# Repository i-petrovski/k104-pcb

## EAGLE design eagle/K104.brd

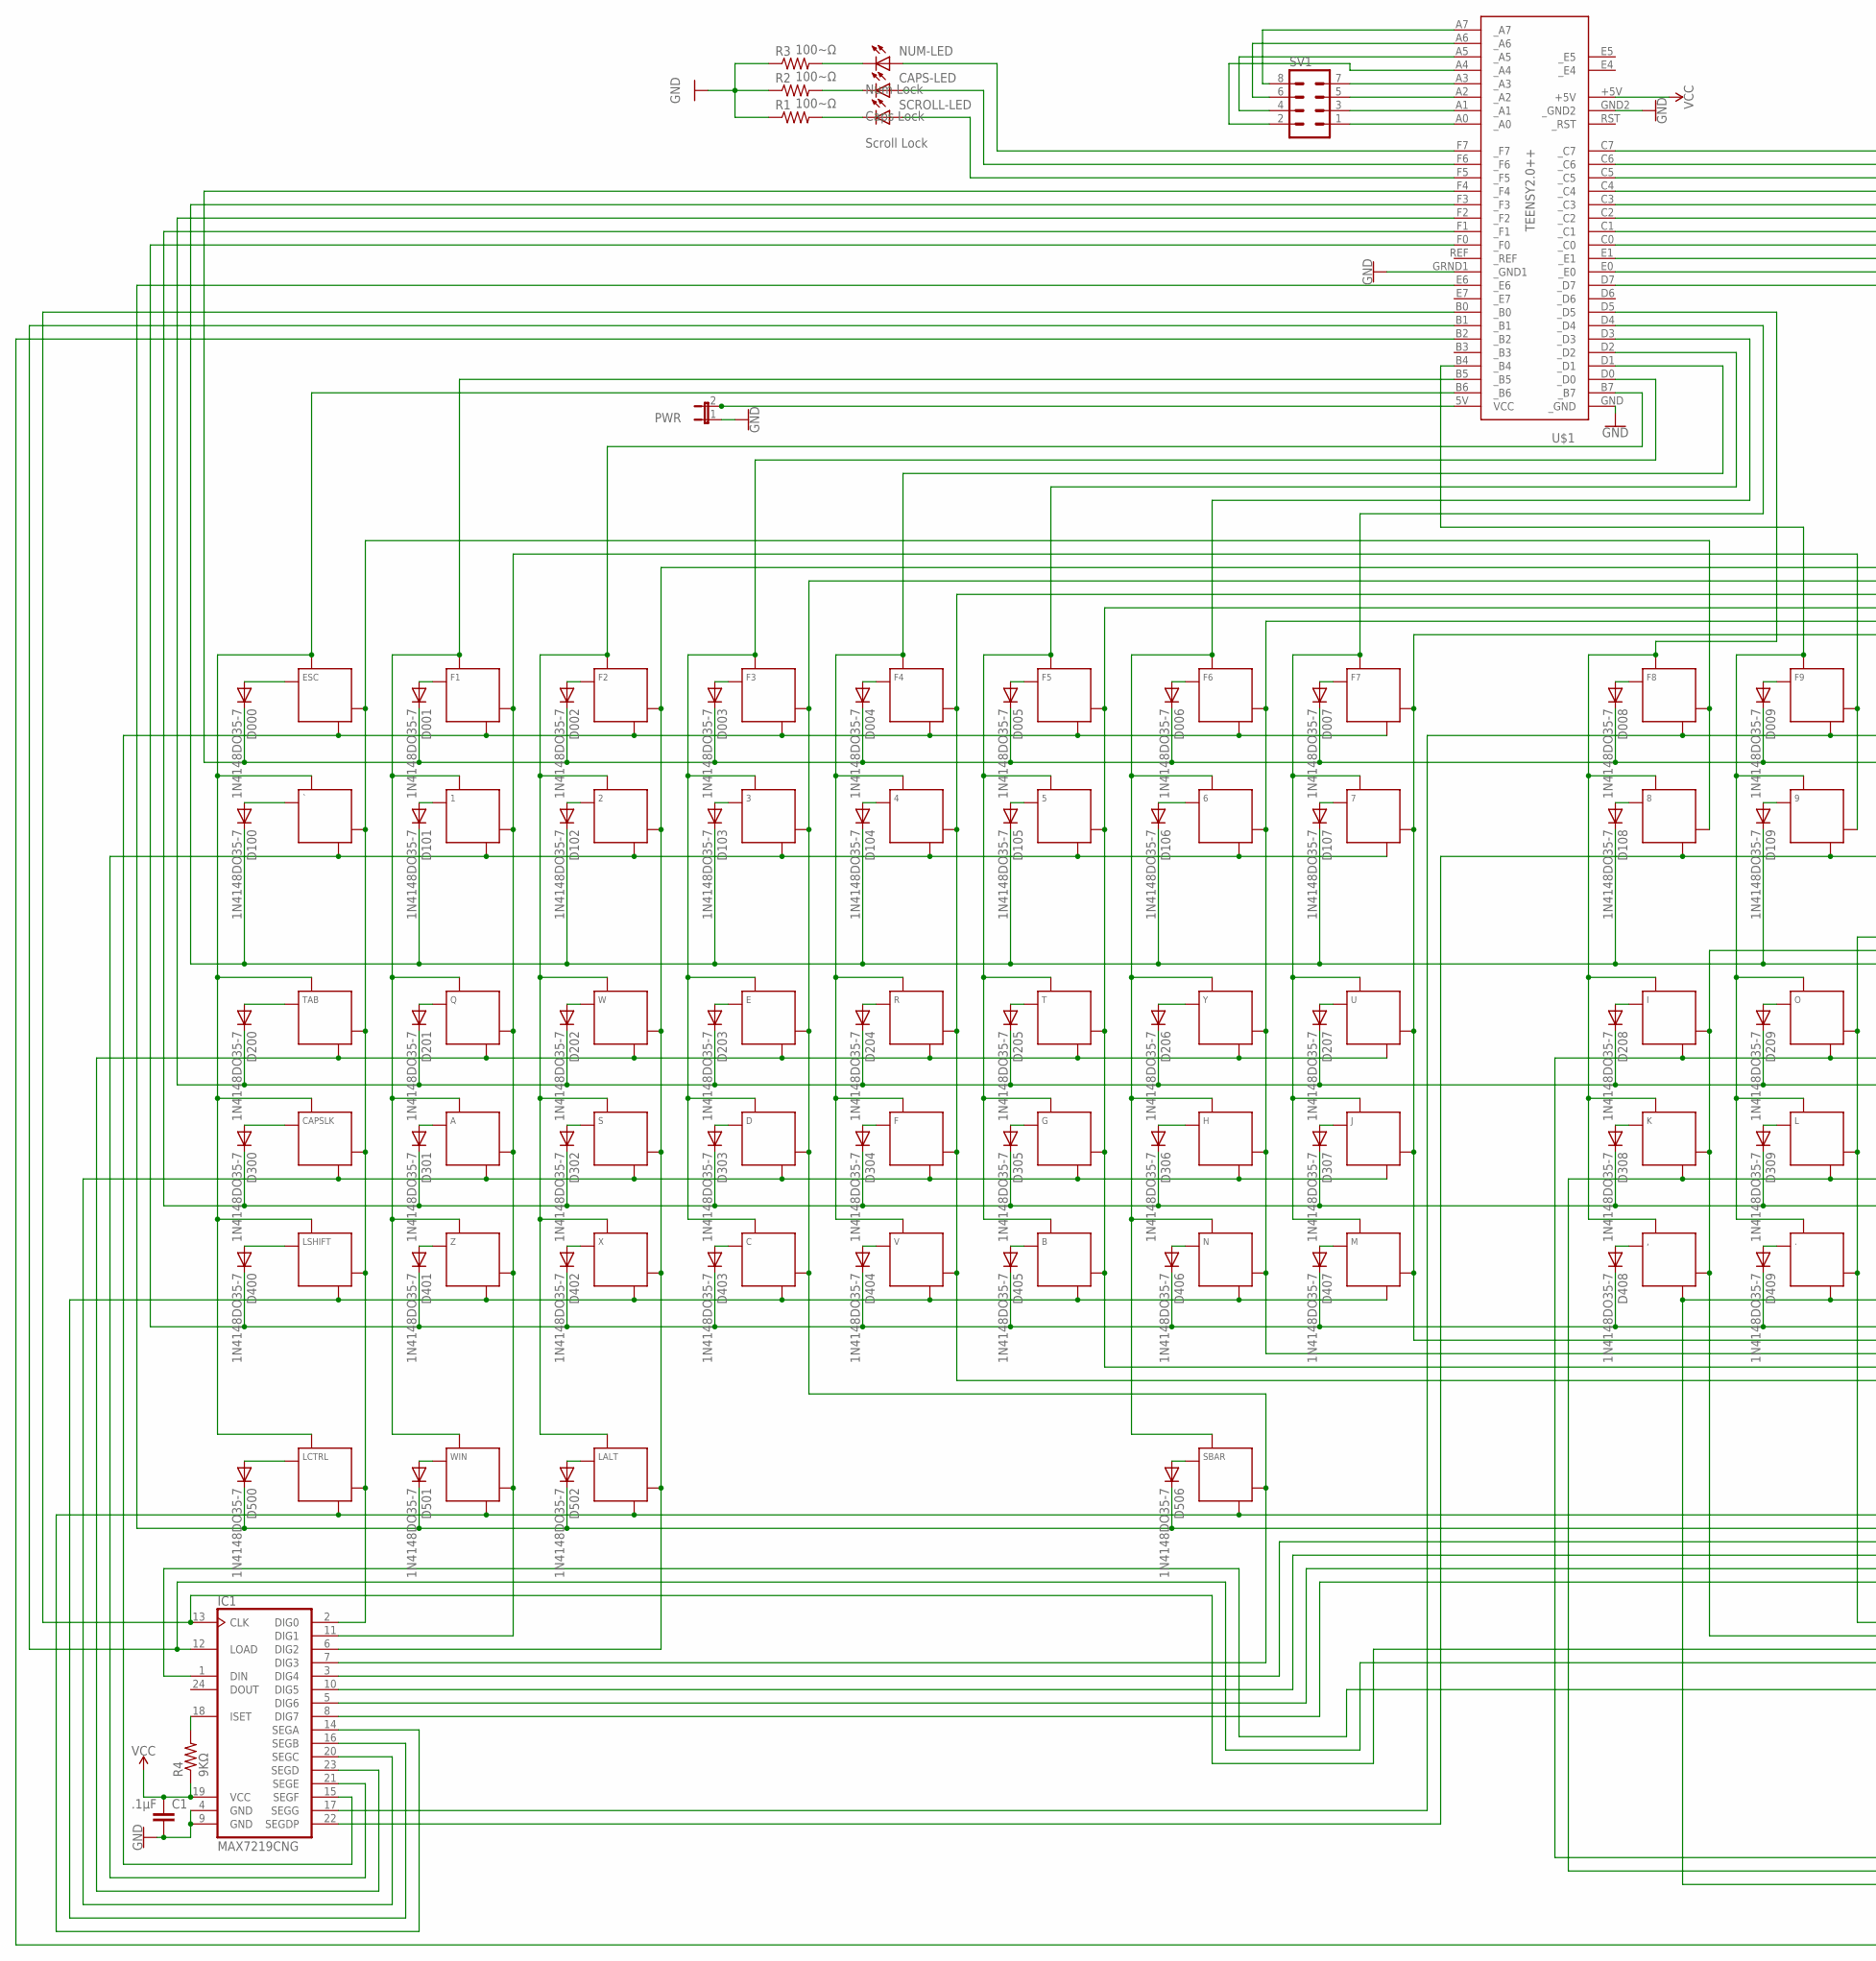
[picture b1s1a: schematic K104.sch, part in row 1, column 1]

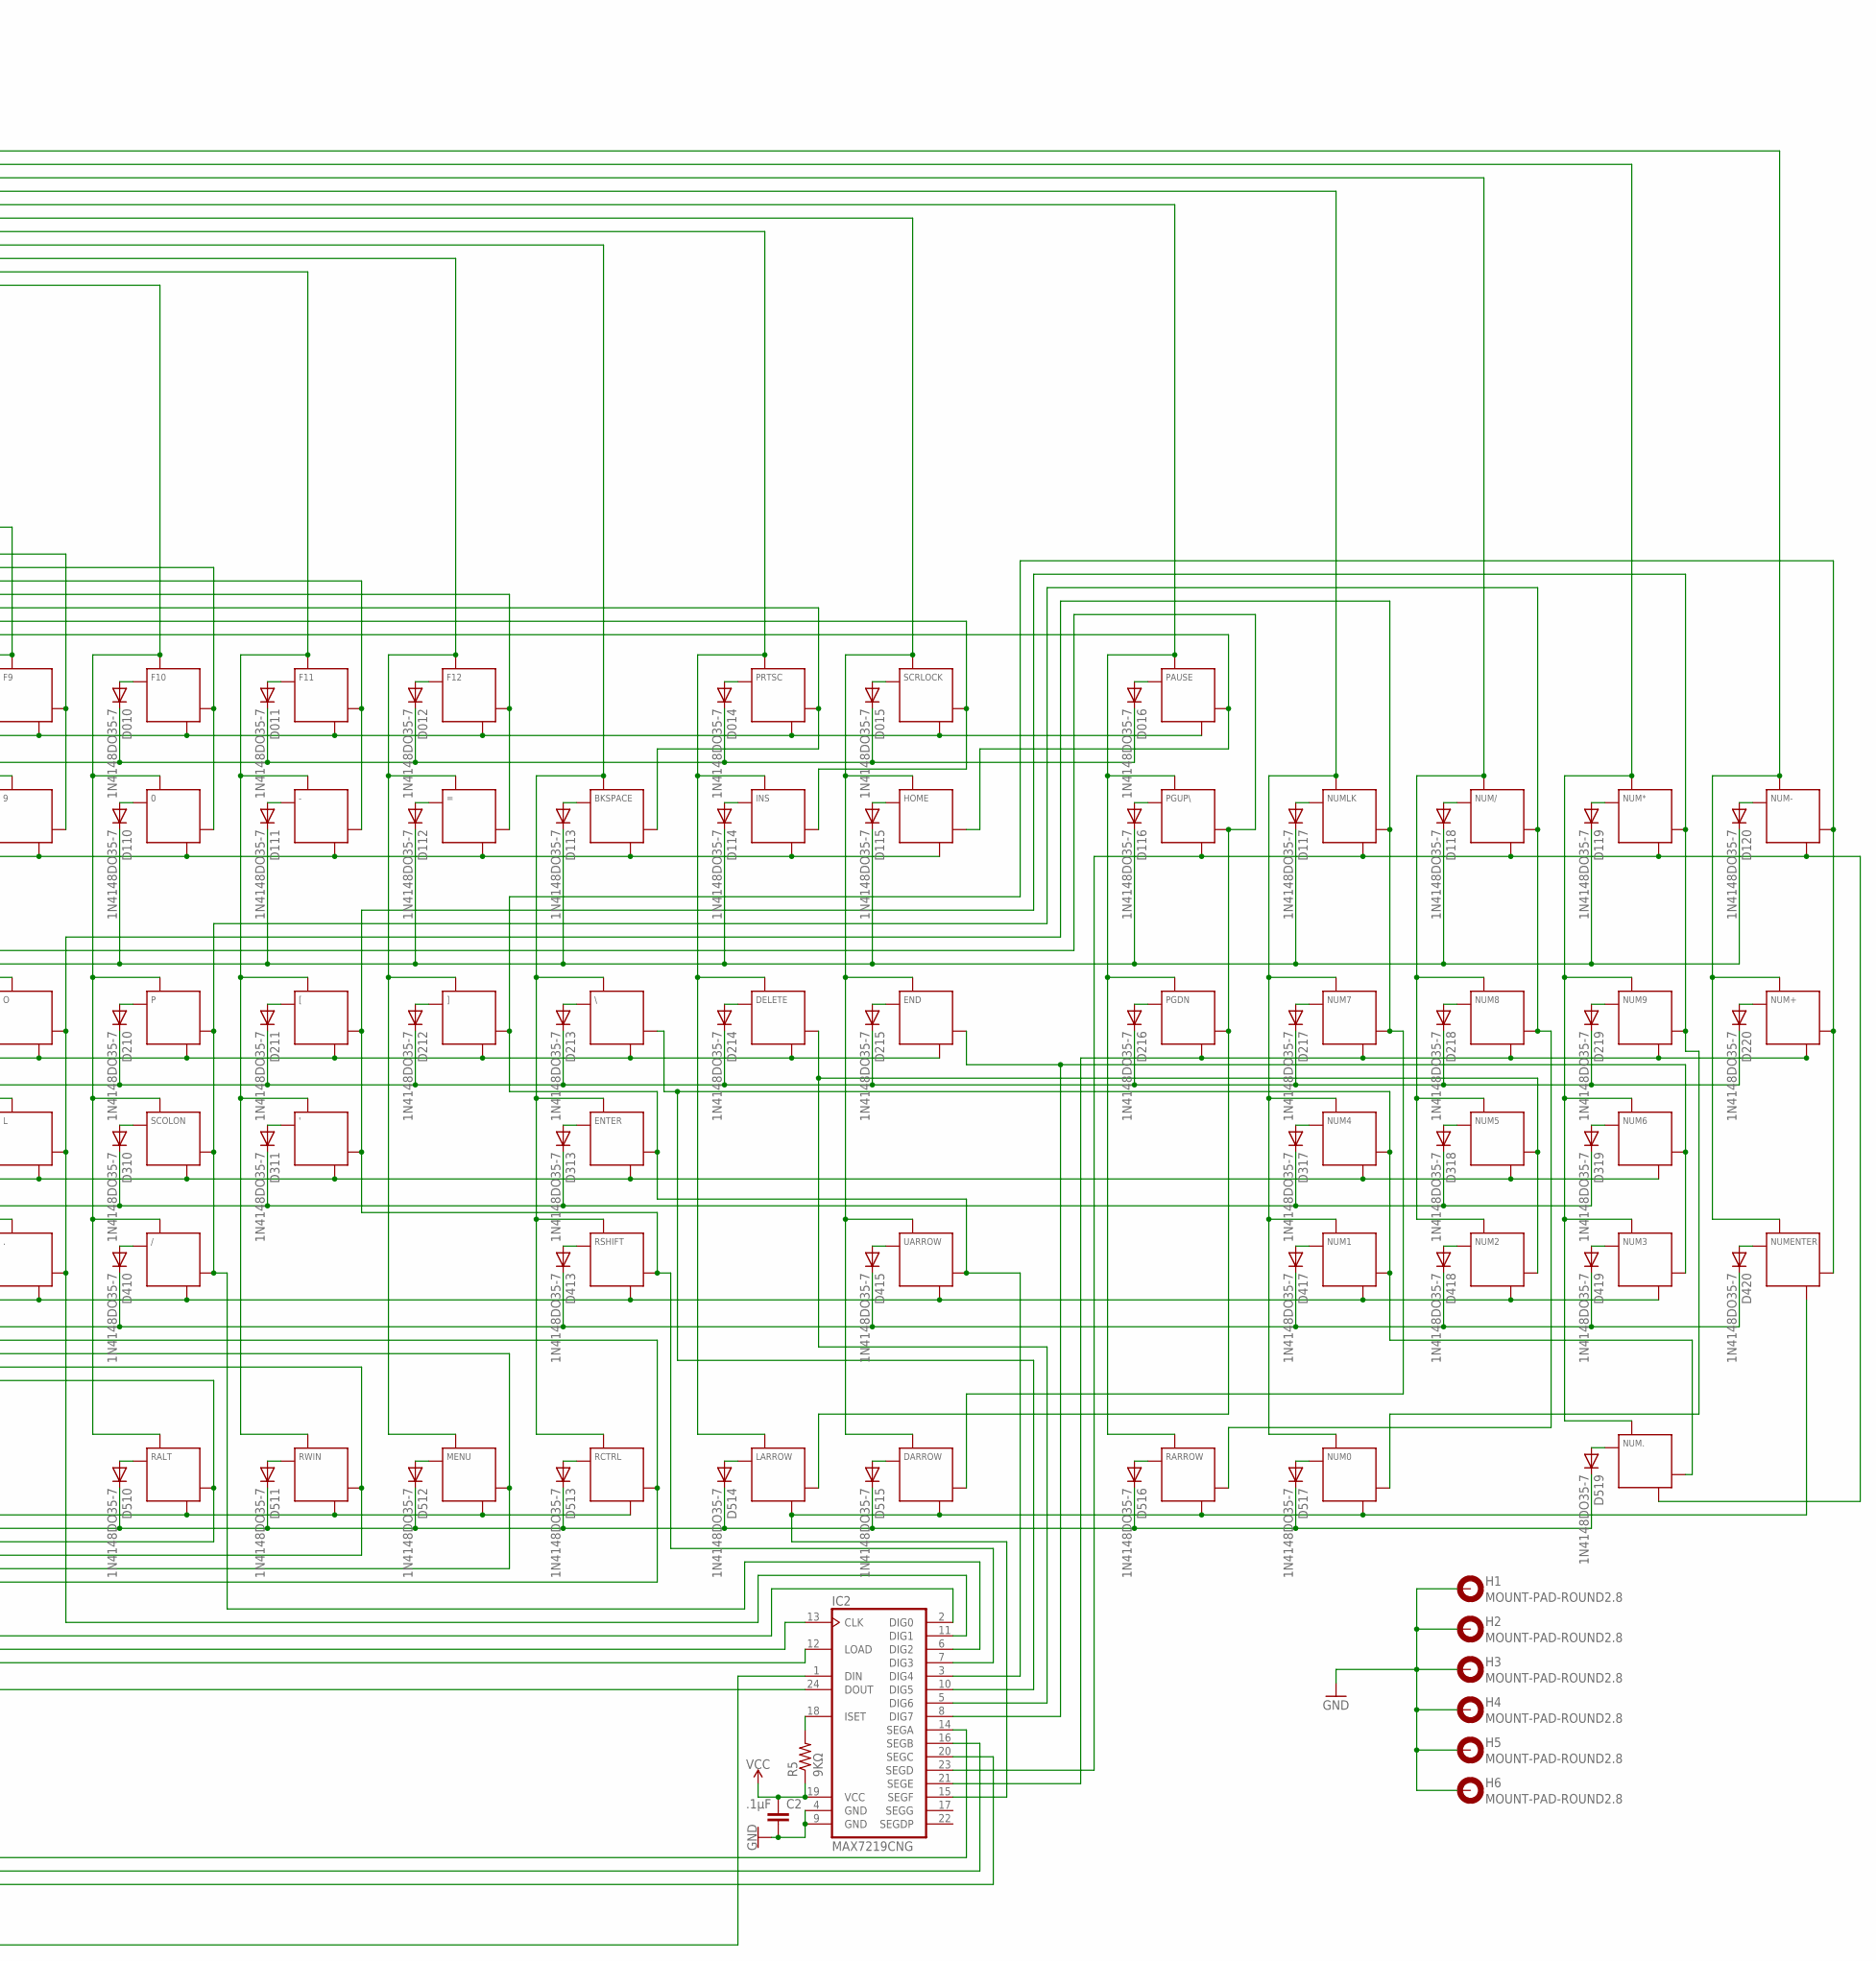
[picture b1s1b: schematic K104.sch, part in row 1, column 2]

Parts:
0, 1, 2, 3, 4, 5, 6, 7, 8, 9, .: KEYSWITCH-LED-MX-1U-LED; MX-1U-LED
': KEYSWITCH-LED-MX-1U-LED; MX-1U-LED
,: KEYSWITCH-LED-MX-1U-LED; MX-1U-LED
-: KEYSWITCH-LED-MX-1U-LED; MX-1U-LED
/: KEYSWITCH-LED-MX-1U-LED; MX-1U-LED
=: KEYSWITCH-LED-MX-1U-LED; MX-1U-LED
A: KEYSWITCH-LED-MX-1U-LED; MX-1U-LED
B: KEYSWITCH-LED-MX-1U-LED; MX-1U-LED
BKSPACE: KEYSWITCH-LED-MX-2U-LED; MX-2U-LED
C: KEYSWITCH-LED-MX-1U-LED; MX-1U-LED
C1, C2: .1μF; C025-024X044
CAPS-LED: Caps Lock; LED3MM
CAPSLK: KEYSWITCH-LED-MX-1U-LED; MX-1U-LED
D: KEYSWITCH-LED-MX-1U-LED; MX-1U-LED
D000, D001, D002, D003, D004, D005, D006, D007, D008, D009, D010, D011, D012, D014, D015, D016, D100, D101, D102, D103, D104, D105, D106, D107, D108, D109, D110, D111, D112, D113, D114, D115, D116, D117, D118, D119, D120, D200, D201, D202, D203, D204, D205, D206, D207, D208, D209, D210, D211, D212, D213, D214, D215, D216, D217, D218, D219, D220, D300, D301, D302, D303, D304, D305, D306, D307, D308, D309, D310, D311, D313, D317, D318, D319, D400, D401, D402, D403, D404, D405, D406, D407, D408, D409, D410, D413, D415, D417, D418, D419, D420, D500, D501, D502, D506, D510, D511, D512, D513, D514, D515, D516, D517, D519: 1N4148DO35-7; DO35-7
DARROW: KEYSWITCH-LED-MX-1U-LED; MX-1U-LED
DELETE: KEYSWITCH-LED-MX-1U-LED; MX-1U-LED
E: KEYSWITCH-LED-MX-1U-LED; MX-1U-LED
END: KEYSWITCH-LED-MX-1U-LED; MX-1U-LED
ENTER: KEYSWITCH-LED-MX-2U-LED; MX-2U-LED
ESC: S001; MX-1U-LED
F, F1, F2, F3, F4, F5, F6, F7, F8, F9, F10, F11, F12: KEYSWITCH-LED-MX-1U-LED; MX-1U-LED
G: KEYSWITCH-LED-MX-1U-LED; MX-1U-LED
H: KEYSWITCH-LED-MX-1U-LED; MX-1U-LED
H1, H2, H3, H4, H5, H6: MOUNT-PAD-ROUND2.8; 2,8-PAD
HOME: KEYSWITCH-LED-MX-1U-LED; MX-1U-LED
I: KEYSWITCH-LED-MX-1U-LED; MX-1U-LED
IC1, IC2: MAX7219CNG; DIL24-3
INS: KEYSWITCH-LED-MX-1U-LED; MX-1U-LED
J: KEYSWITCH-LED-MX-1U-LED; MX-1U-LED
K: KEYSWITCH-LED-MX-1U-LED; MX-1U-LED
L: KEYSWITCH-LED-MX-1U-LED; MX-1U-LED
LALT: KEYSWITCH-LED-MX-1U-LED; MX-1U-LED
LARROW: KEYSWITCH-LED-MX-1U-LED; MX-1U-LED
LCTRL: KEYSWITCH-LED-MX-1U-LED; MX-1U-LED
LSHIFT: KEYSWITCH-LED-MX-2U-LED; MX-2U-LED
M: KEYSWITCH-LED-MX-1U-LED; MX-1U-LED
MENU: KEYSWITCH-LED-MX-1U-LED; MX-1U-LED
N: KEYSWITCH-LED-MX-1U-LED; MX-1U-LED
NUM0: KEYSWITCH-LED-MX-2U-LED; MX-2U-LED
NUM1, NUM2, NUM3, NUM4, NUM5, NUM6, NUM7, NUM8, NUM9, NUM.: KEYSWITCH-LED-MX-1U-LED; MX-1U-LED
NUM*: KEYSWITCH-LED-MX-1U-LED; MX-1U-LED
NUM+: KEYSWITCH-LED-MX-2U-LED; MX-2U-LED
NUM-: KEYSWITCH-LED-MX-1U-LED; MX-1U-LED
NUM-LED: Num Lock; LED3MM
NUM/: KEYSWITCH-LED-MX-1U-LED; MX-1U-LED
NUMENTER: KEYSWITCH-LED-MX-2U-LED; MX-2U-LED
NUMLK: KEYSWITCH-LED-MX-1U-LED; MX-1U-LED
O: KEYSWITCH-LED-MX-1U-LED; MX-1U-LED
P: KEYSWITCH-LED-MX-1U-LED; MX-1U-LED
PAUSE: KEYSWITCH-LED-MX-1U-LED; MX-1U-LED
PGDN: KEYSWITCH-LED-MX-1U-LED; MX-1U-LED
PGUP\: KEYSWITCH-LED-MX-1U-LED; MX-1U-LED
PRTSC: KEYSWITCH-LED-MX-1U-LED; MX-1U-LED
PWR: JP1E; JP1
Q: KEYSWITCH-LED-MX-1U-LED; MX-1U-LED
R: KEYSWITCH-LED-MX-1U-LED; MX-1U-LED
R1, R2, R3: 100~Ω; 0204/7
R4, R5: 9KΩ; 0204/7
RALT: KEYSWITCH-LED-MX-1U-LED; MX-1U-LED
RARROW: KEYSWITCH-LED-MX-1U-LED; MX-1U-LED
RCTRL: KEYSWITCH-LED-MX-1U-LED; MX-1U-LED
RSHIFT: KEYSWITCH-LED-MX-2U-LED; MX-2U-LED
RWIN: KEYSWITCH-LED-MX-1U-LED; MX-1U-LED
S: KEYSWITCH-LED-MX-1U-LED; MX-1U-LED
SBAR: KEYSWITCH-LED-MX-6.25U-LED; MX-6.25U-LED
SCOLON: KEYSWITCH-LED-MX-1U-LED; MX-1U-LED
SCRLOCK: KEYSWITCH-LED-MX-1U-LED; MX-1U-LED
SCROLL-LED: Scroll Lock; LED3MM
SV1: MA04-2
T: KEYSWITCH-LED-MX-1U-LED; MX-1U-LED
TAB: KEYSWITCH-LED-MX-1U-LED; MX-1U-LED
U: KEYSWITCH-LED-MX-1U-LED; MX-1U-LED
U$1: TEENSY2.0++
UARROW: KEYSWITCH-LED-MX-1U-LED; MX-1U-LED
V: KEYSWITCH-LED-MX-1U-LED; MX-1U-LED
W: KEYSWITCH-LED-MX-1U-LED; MX-1U-LED
WIN: KEYSWITCH-LED-MX-1U-LED; MX-1U-LED
X: KEYSWITCH-LED-MX-1U-LED; MX-1U-LED
Y: KEYSWITCH-LED-MX-1U-LED; MX-1U-LED
Z: KEYSWITCH-LED-MX-1U-LED; MX-1U-LED
[: KEYSWITCH-LED-MX-1U-LED; MX-1U-LED
\\: KEYSWITCH-LED-MX-1U-LED; MX-1U-LED
]: KEYSWITCH-LED-MX-1U-LED; MX-1U-LED
`: KEYSWITCH-LED-MX-1U-LED; MX-1U-LED

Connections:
A0: SV1.1, U$1.A0 (_A0)
A1: SV1.3, U$1.A1 (_A1)
A2: SV1.5, U$1.A2 (_A2)
A3: SV1.7, U$1.A3 (_A3)
A4: SV1.2, U$1.A4 (_A4)
A5: SV1.4, U$1.A5 (_A5)
A6: SV1.6, U$1.A6 (_A6)
A7: SV1.8, U$1.A7 (_A7)
B0: IC1.13 (CLK), IC2.13 (CLK), U$1.B0 (_B0)
B1: IC1.12 (LOAD), IC2.12 (LOAD), U$1.B1 (_B1)
B2: IC2.1 (DIN), U$1.B2 (_B2)
B5: 1.MX2 (P1), A.MX2 (P1), F1.MX2 (P1), Q.MX2 (P1), U$1.B5 (_B5), WIN.MX2 (P1), Z.MX2 (P1)
B6: CAPSLK.MX2 (P1), ESC.MX2 (P1), LCTRL.MX2 (P1), LSHIFT.MX2 (P1), TAB.MX2 (P1), U$1.B6 (_B6), `.MX2 (P1)
B7: 2.MX2 (P1), F2.MX2 (P1), LALT.MX2 (P1), S.MX2 (P1), U$1.B7 (_B7), W.MX2 (P1), X.MX2 (P1)
C0: BKSPACE.MX2 (P1), ENTER.MX2 (P1), RCTRL.MX2 (P1), RSHIFT.MX2 (P1), U$1.C0 (_C0), \\.MX2 (P1)
C1: DELETE.MX2 (P1), INS.MX2 (P1), LARROW.MX2 (P1), PRTSC.MX2 (P1), U$1.C1 (_C1)
C2: DARROW.MX2 (P1), END.MX2 (P1), HOME.MX2 (P1), SCRLOCK.MX2 (P1), U$1.C2 (_C2), UARROW.MX2 (P1)
C3: PAUSE.MX2 (P1), PGDN.MX2 (P1), PGUP\.MX2 (P1), RARROW.MX2 (P1), U$1.C3 (_C3)
C4: NUM0.MX2 (P1), NUM1.MX2 (P1), NUM4.MX2 (P1), NUM7.MX2 (P1), NUMLK.MX2 (P1), U$1.C4 (_C4)
C5: NUM2.MX2 (P1), NUM5.MX2 (P1), NUM8.MX2 (P1), NUM/.MX2 (P1), U$1.C5 (_C5)
C6: NUM3.MX2 (P1), NUM6.MX2 (P1), NUM9.MX2 (P1), NUM*.MX2 (P1), NUM..MX2 (P1), U$1.C6 (_C6)
C7: NUM+.MX2 (P1), NUM-.MX2 (P1), NUMENTER.MX2 (P1), U$1.C7 (_C7)
D0: 3.MX2 (P1), C.MX2 (P1), D.MX2 (P1), E.MX2 (P1), F3.MX2 (P1), U$1.D0 (_D0)
D1: 4.MX2 (P1), F.MX2 (P1), F4.MX2 (P1), R.MX2 (P1), U$1.D1 (_D1), V.MX2 (P1)
D2: 5.MX2 (P1), B.MX2 (P1), F5.MX2 (P1), G.MX2 (P1), T.MX2 (P1), U$1.D2 (_D2)
D3: 6.MX2 (P1), F6.MX2 (P1), H.MX2 (P1), N.MX2 (P1), SBAR.MX2 (P1), U$1.D3 (_D3), Y.MX2 (P1)
D4: 7.MX2 (P1), F7.MX2 (P1), J.MX2 (P1), M.MX2 (P1), U.MX2 (P1), U$1.D4 (_D4)
D5: 8.MX2 (P1), ,.MX2 (P1), F8.MX2 (P1), I.MX2 (P1), K.MX2 (P1), U$1.D5 (_D5)
D6: 9.MX2 (P1), ..MX2 (P1), F9.MX2 (P1), L.MX2 (P1), O.MX2 (P1), U$1.B4 (_B4)
D7: 0.MX2 (P1), /.MX2 (P1), F10.MX2 (P1), P.MX2 (P1), RALT.MX2 (P1), SCOLON.MX2 (P1), U$1.D7 (_D7)
E0: '.MX2 (P1), -.MX2 (P1), F11.MX2 (P1), RWIN.MX2 (P1), U$1.E0 (_E0), [.MX2 (P1)
E1: =.MX2 (P1), F12.MX2 (P1), MENU.MX2 (P1), U$1.E1 (_E1), ].MX2 (P1)
E6: D500.C, D501.C, D502.C, D506.C, D510.C, D511.C, D512.C, D513.C, D514.C, D515.C, D516.C, D517.C, D519.C, U$1.E6 (_E6)
F0: D400.C, D401.C, D402.C, D403.C, D404.C, D405.C, D406.C, D407.C, D408.C, D409.C, D410.C, D413.C, D415.C, D417.C, D418.C, D419.C, D420.C, U$1.F0 (_F0)
F1: D300.C, D301.C, D302.C, D303.C, D304.C, D305.C, D306.C, D307.C, D308.C, D309.C, D310.C, D311.C, D313.C, D317.C, D318.C, D319.C, U$1.F1 (_F1)
F2: D200.C, D201.C, D202.C, D203.C, D204.C, D205.C, D206.C, D207.C, D208.C, D209.C, D210.C, D211.C, D212.C, D213.C, D214.C, D215.C, D216.C, D217.C, D218.C, D219.C, D220.C, U$1.F2 (_F2)
F3: D100.C, D101.C, D102.C, D103.C, D104.C, D105.C, D106.C, D107.C, D108.C, D109.C, D110.C, D111.C, D112.C, D113.C, D114.C, D115.C, D116.C, D117.C, D118.C, D119.C, D120.C, U$1.F3 (_F3)
F4: D000.C, D001.C, D002.C, D003.C, D004.C, D005.C, D006.C, D007.C, D008.C, D009.C, D010.C, D011.C, D012.C, D014.C, D015.C, D016.C, U$1.F4 (_F4)
F5: SCROLL-LED.A, U$1.F5 (_F5)
F6: CAPS-LED.A, U$1.F6 (_F6)
F7: NUM-LED.A, U$1.F7 (_F7)
GND: C1.2, C2.2, H1.B2,8, H2.B2,8, H3.B2,8, H4.B2,8, H5.B2,8, H6.B2,8, IC1.4 (GND), IC1.9 (GND), IC2.4 (GND), IC2.9 (GND), PWR.1, R1.1, R2.1, R3.1, U$1.GND (_GND), U$1.GND2 (_GND2), U$1.GRND1 (_GND1)
IC1-2: 8.LED-, CAPSLK.LED-, ESC.LED-, F8.LED-, IC1.2 (DIG0), LCTRL.LED-, LSHIFT.LED-, TAB.LED-, `.LED-
IC1-3: 4.LED-, =.LED-, F.LED-, F4.LED-, F12.LED-, IC1.3 (DIG4), R.LED-, RALT.LED-, V.LED-
IC1-5: 6.LED-, F6.LED-, H.LED-, IC1.5 (DIG6), INS.LED-, MENU.LED-, N.LED-, SCRLOCK.LED-, Y.LED-
IC1-6: 0.LED-, 2.LED-, F2.LED-, F10.LED-, IC1.6 (DIG2), LALT.LED-, S.LED-, W.LED-, X.LED-
IC1-7: 3.LED-, -.LED-, C.LED-, D.LED-, E.LED-, F3.LED-, F11.LED-, IC1.7 (DIG3), SBAR.LED-
IC1-8: 7.LED-, F7.LED-, HOME.LED-, IC1.8 (DIG7), J.LED-, M.LED-, PAUSE.LED-, RCTRL.LED-, U.LED-
IC1-10: 5.LED-, B.LED-, BKSPACE.LED-, F5.LED-, G.LED-, IC1.10 (DIG5), PRTSC.LED-, RWIN.LED-, T.LED-
IC1-11: 1.LED-, 9.LED-, A.LED-, F1.LED-, F9.LED-, IC1.11 (DIG1), Q.LED-, WIN.LED-, Z.LED-
IC1-14: IC1.14 (SEGA), LALT.LED+, LCTRL.LED+, MENU.LED+, RALT.LED+, RCTRL.LED+, RWIN.LED+, SBAR.LED+, WIN.LED+
IC1-15: ESC.LED+, F1.LED+, F2.LED+, F3.LED+, F4.LED+, F5.LED+, F6.LED+, F7.LED+, IC1.15 (SEGF)
IC1-16: B.LED+, C.LED+, IC1.16 (SEGB), LSHIFT.LED+, M.LED+, N.LED+, V.LED+, X.LED+, Z.LED+
IC1-17: F8.LED+, F9.LED+, F10.LED+, F11.LED+, F12.LED+, IC1.17 (SEGG), PAUSE.LED+, PRTSC.LED+, SCRLOCK.LED+
IC1-20: A.LED+, CAPSLK.LED+, D.LED+, F.LED+, G.LED+, H.LED+, IC1.20 (SEGC), J.LED+, S.LED+
IC1-21: 1.LED+, 2.LED+, 3.LED+, 4.LED+, 5.LED+, 6.LED+, 7.LED+, IC1.21 (SEGE), `.LED+
IC1-22: 0.LED+, 8.LED+, 9.LED+, -.LED+, =.LED+, BKSPACE.LED+, HOME.LED+, IC1.22 (SEGDP), INS.LED+
IC1-23: E.LED+, IC1.23 (SEGD), Q.LED+, R.LED+, T.LED+, TAB.LED+, U.LED+, W.LED+, Y.LED+
IC2-2: ,.LED-, I.LED-, IC2.2 (DIG0), K.LED-, LARROW.LED-, PGDN.LED-, PGUP\.LED-
IC2-3: ENTER.LED-, IC2.3 (DIG4), NUM+.LED-, NUM-.LED-, NUMENTER.LED-, UARROW.LED-, ].LED-
IC2-5: DELETE.LED-, IC2.5 (DIG6), NUM2.LED-, NUM5.LED-
IC2-6: /.LED-, IC2.6 (DIG2), NUM8.LED-, NUM/.LED-, P.LED-, RARROW.LED-, SCOLON.LED-
IC2-7: '.LED-, IC2.7 (DIG3), NUM0.LED-, NUM9.LED-, NUM*.LED-, RSHIFT.LED-, [.LED-
IC2-8: END.LED-, IC2.8 (DIG7), NUM3.LED-, NUM6.LED-
IC2-10: IC2.10 (DIG5), NUM1.LED-, NUM4.LED-, NUM..LED-, \\.LED-
IC2-11: ..LED-, DARROW.LED-, IC2.11 (DIG1), L.LED-, NUM7.LED-, NUMLK.LED-, O.LED-
IC2-14: DELETE.LED+, END.LED+, I.LED+, IC2.14 (SEGA), O.LED+, P.LED+, [.LED+, \\.LED+, ].LED+
IC2-15: DARROW.LED+, IC2.15 (SEGF), LARROW.LED+, NUM0.LED+, NUMENTER.LED+, RARROW.LED+
IC2-16: '.LED+, ENTER.LED+, IC2.16 (SEGB), K.LED+, L.LED+, NUM4.LED+, NUM5.LED+, NUM6.LED+, SCOLON.LED+
IC2-20: ,.LED+, ..LED+, /.LED+, IC2.20 (SEGC), NUM1.LED+, NUM2.LED+, NUM3.LED+, RSHIFT.LED+, UARROW.LED+
IC2-21: IC2.21 (SEGE), NUM7.LED+, NUM8.LED+, NUM9.LED+, NUM+.LED+, PGDN.LED+
IC2-23: IC2.23 (SEGD), NUM*.LED+, NUM-.LED+, NUM..LED+, NUM/.LED+, NUMLK.LED+, PGUP\.LED+
IC2-DOUT: IC1.1 (DIN), IC2.24 (DOUT)
unnamed: D000.A, ESC.MX1 (P0)
unnamed: D001.A, F1.MX1 (P0)
unnamed: D002.A, F2.MX1 (P0)
unnamed: D116.A, PGUP\.MX1 (P0)
unnamed: D003.A, F3.MX1 (P0)
unnamed: D004.A, F4.MX1 (P0)
unnamed: D100.A, `.MX1 (P0)
unnamed: D011.A, F11.MX1 (P0)
unnamed: D005.A, F5.MX1 (P0)
unnamed: D006.A, F6.MX1 (P0)
unnamed: D007.A, F7.MX1 (P0)
unnamed: D008.A, F8.MX1 (P0)
unnamed: D009.A, F9.MX1 (P0)
unnamed: D014.A, PRTSC.MX1 (P0)
unnamed: D010.A, F10.MX1 (P0)
unnamed: 1.MX1 (P0), D101.A
unnamed: D012.A, F12.MX1 (P0)
unnamed: D015.A, SCRLOCK.MX1 (P0)
unnamed: 2.MX1 (P0), D102.A
unnamed: D016.A, PAUSE.MX1 (P0)
unnamed: 3.MX1 (P0), D103.A
unnamed: 7.MX1 (P0), D107.A
unnamed: 4.MX1 (P0), D104.A
unnamed: 5.MX1 (P0), D105.A
unnamed: 6.MX1 (P0), D106.A
unnamed: 8.MX1 (P0), D108.A
unnamed: 9.MX1 (P0), D109.A
unnamed: 0.MX1 (P0), D110.A
unnamed: -.MX1 (P0), D111.A
unnamed: =.MX1 (P0), D112.A
unnamed: BKSPACE.MX1 (P0), D113.A
unnamed: D201.A, Q.MX1 (P0)
unnamed: D200.A, TAB.MX1 (P0)
unnamed: D308.A, K.MX1 (P0)
unnamed: D202.A, W.MX1 (P0)
unnamed: D302.A, S.MX1 (P0)
unnamed: A.MX1 (P0), D301.A
unnamed: D402.A, X.MX1 (P0)
unnamed: D401.A, Z.MX1 (P0)
unnamed: C.MX1 (P0), D403.A
unnamed: D304.A, F.MX1 (P0)
unnamed: D204.A, R.MX1 (P0)
unnamed: D404.A, V.MX1 (P0)
unnamed: B.MX1 (P0), D405.A
unnamed: D305.A, G.MX1 (P0)
unnamed: D.MX1 (P0), D303.A
unnamed: D205.A, T.MX1 (P0)
unnamed: D206.A, Y.MX1 (P0)
unnamed: D207.A, U.MX1 (P0)
unnamed: D307.A, J.MX1 (P0)
unnamed: D407.A, M.MX1 (P0)
unnamed: D406.A, N.MX1 (P0)
unnamed: D306.A, H.MX1 (P0)
unnamed: D208.A, I.MX1 (P0)
unnamed: D209.A, O.MX1 (P0)
unnamed: D309.A, L.MX1 (P0)
unnamed: ..MX1 (P0), D409.A
unnamed: ,.MX1 (P0), D408.A
unnamed: /.MX1 (P0), D410.A
unnamed: D310.A, SCOLON.MX1 (P0)
unnamed: D210.A, P.MX1 (P0)
unnamed: D211.A, [.MX1 (P0)
unnamed: '.MX1 (P0), D311.A
unnamed: D400.A, LSHIFT.MX1 (P0)
unnamed: D212.A, ].MX1 (P0)
unnamed: D213.A, \\.MX1 (P0)
unnamed: D313.A, ENTER.MX1 (P0)
unnamed: D216.A, PGDN.MX1 (P0)
unnamed: D215.A, END.MX1 (P0)
unnamed: D214.A, DELETE.MX1 (P0)
unnamed: D415.A, UARROW.MX1 (P0)
unnamed: D516.A, RARROW.MX1 (P0)
unnamed: D515.A, DARROW.MX1 (P0)
unnamed: D514.A, LARROW.MX1 (P0)
unnamed: D413.A, RSHIFT.MX1 (P0)
unnamed: D512.A, MENU.MX1 (P0)
unnamed: D511.A, RWIN.MX1 (P0)
unnamed: D510.A, RALT.MX1 (P0)
unnamed: CAPSLK.MX1 (P0), D300.A
unnamed: D203.A, E.MX1 (P0)
unnamed: NUM-LED.K (C), R3.2
unnamed: CAPS-LED.K (C), R2.2
unnamed: D500.A, LCTRL.MX1 (P0)
unnamed: D501.A, WIN.MX1 (P0)
unnamed: D502.A, LALT.MX1 (P0)
unnamed: D506.A, SBAR.MX1 (P0)
unnamed: R1.2, SCROLL-LED.K (C)
unnamed: D114.A, INS.MX1 (P0)
unnamed: D115.A, HOME.MX1 (P0)
unnamed: D513.A, RCTRL.MX1 (P0)
unnamed: D217.A, NUM7.MX1 (P0)
unnamed: D117.A, NUMLK.MX1 (P0)
unnamed: D517.A, NUM0.MX1 (P0)
unnamed: D417.A, NUM1.MX1 (P0)
unnamed: D317.A, NUM4.MX1 (P0)
unnamed: D218.A, NUM8.MX1 (P0)
unnamed: D118.A, NUM/.MX1 (P0)
unnamed: D418.A, NUM2.MX1 (P0)
unnamed: D318.A, NUM5.MX1 (P0)
unnamed: D219.A, NUM9.MX1 (P0)
unnamed: D119.A, NUM*.MX1 (P0)
unnamed: D519.A, NUM..MX1 (P0)
unnamed: D419.A, NUM3.MX1 (P0)
unnamed: D319.A, NUM6.MX1 (P0)
unnamed: D220.A, NUM+.MX1 (P0)
unnamed: D120.A, NUM-.MX1 (P0)
unnamed: D420.A, NUMENTER.MX1 (P0)
unnamed: IC1.18 (ISET), R4.2
unnamed: IC2.18 (ISET), R5.2
VCC: C1.1, C2.1, IC1.19 (VCC), IC2.19 (VCC), R4.1, R5.1, U$1.+5V
VCC2: PWR.2, U$1.5V (VCC)

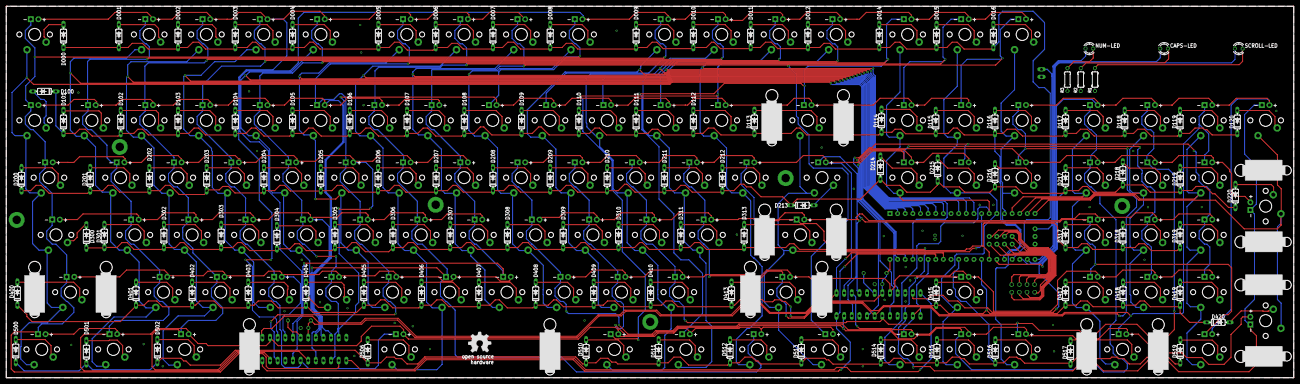
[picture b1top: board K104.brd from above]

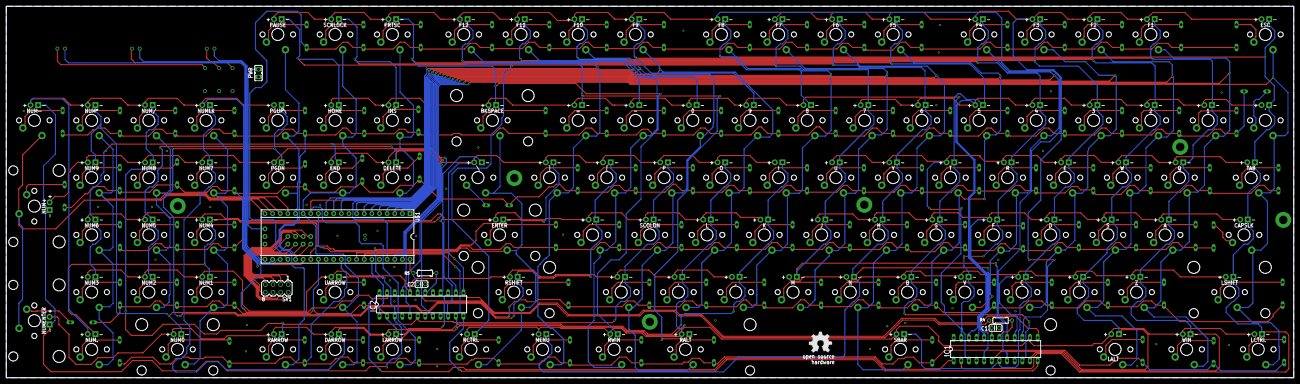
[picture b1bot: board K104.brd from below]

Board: 2 copper layers, 428.3 x 123.6 mm, 231 parts (10 on the bottom side), 184 nets.

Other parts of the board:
U$2, U$3: OSHW_8MM

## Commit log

2019-05-31 k104 pcb files
2019-05-31 k104 case dwg
2019-05-31 add PCB and case files

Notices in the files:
parts and their libraries:
SparkFun-PowerSymbols: Licensing: Creative Commons ShareAlike 4.0 International - https://creativecommons.org/licenses/by-sa/4.0
